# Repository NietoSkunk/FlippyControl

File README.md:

# FlippyControl

Arduino / ESP32 Shield for controlling the [Luminator MAX3000](https://github.com/NietoSkunk/FlippyDriver) Flip Dot driver.

In addition to connecting the appropriate pins of the microcontroller to the data harness, it also includes pads to connect two Wii Extension Controllers (including Classic Controller, Pro Controller, etc), a USB-C 5V power input, and selectable Vcc outputs.

## Cloning repository (with Submodules)

```bash
$ git clone --recurse-submodules git@github.com:NietoSkunk/FlippyControl.git
```

## Production notes

* Only one MCU should be connected at a time.

## Data Harness

| Pin | # | # | Pin |
| --- | - | - | --- |
| VCC | 1 | 2 | GND |
| MOSI | 3 | 4 | PULSE_ENABLE |
| LATCH | 5 | 6 | COL_PULSE_N |
| CLK | 7 | 8 | ROW_PULSE_N |
| RESET | 9 | 10 | LED PWM |
| 5V Return | 11 | 12 | GND |

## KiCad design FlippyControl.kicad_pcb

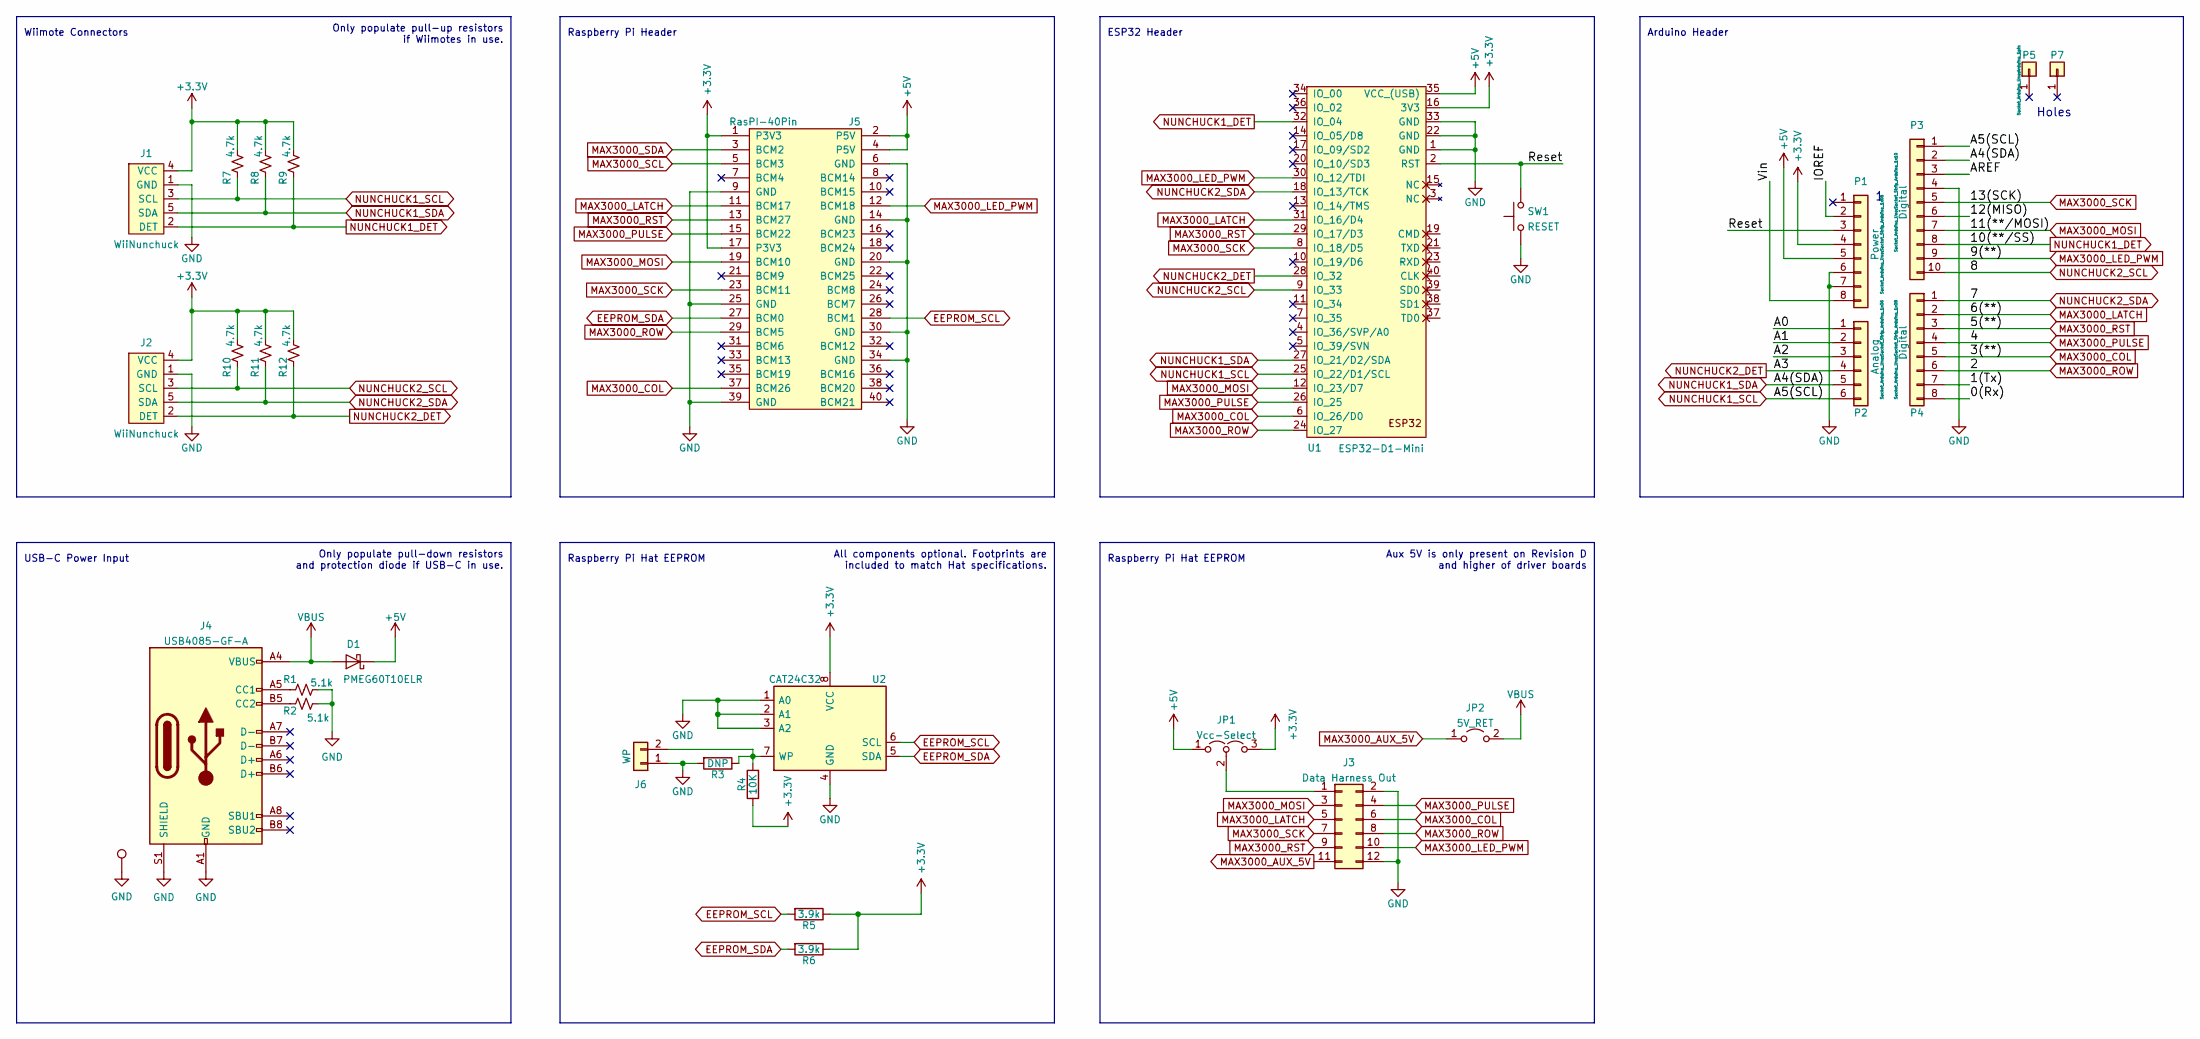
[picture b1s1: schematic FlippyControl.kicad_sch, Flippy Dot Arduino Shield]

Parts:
D1: PMEG60T10ELR; D_SOD-123
J1, J2: WiiNunchuck
J3: Data Harness Out; IDC-Header_2x06_P2.54mm_Vertical
J4: USB4085-GF-A; USB_C_Receptacle_GCT_USB4085
J5: RasPI-40Pin; IDC-Header_2x20_P2.54mm_Vertical
J6: WP; PinHeader_1x02_P2.54mm_Vertical
JP1: Vcc-Select; PinHeader_1x03_P2.54mm_Vertical
JP2: 5V_RET; PinHeader_1x02_P2.54mm_Vertical
P1: Power; Socket_Strip_Arduino_1x08
P2: Analog; Socket_Strip_Arduino_1x06
P3: Digital; Socket_Strip_Arduino_1x10
P4: Digital; Socket_Strip_Arduino_1x08
P5, P7: CONN_01X01; Arduino_1pin
R1, R2: 5.1k; R_0603_1608Metric
R3: DNP; R_0603_1608Metric
R4: 10K; R_0603_1608Metric
R5, R6: 3.9k; R_0603_1608Metric
R7, R8, R9, R10, R11, R12: 4.7k; R_0603_1608Metric
SW1: RESET; SW_SPST_PTS645
TP7: GND; TestPoint_Keystone_5005-5009_Compact
U1: ESP32-D1-Mini; ESP32_mini
U2: CAT24C32; SOIC-8_3.9x4.9mm_P1.27mm

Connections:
+3V3: J1.4 (VCC), J2.4 (VCC), J5.1 (P3V3), J5.17 (P3V3), JP1.3 (B), P1.4, R4.1, R5.1, R6.1, R7.2, R8.2, R9.2, R10.2, R11.2, R12.2, U1.16 (3V3), U2.8 (VCC)
+5V: D1.1 (K), J5.2 (P5V), J5.4 (P5V), JP1.1 (A), P1.5, U1.35 (VCC_(USB))
/0(Rx): P4.8
/1(Tx): P4.7
/12(MISO): P3.6
/A0: P2.1
/A1: P2.2
/A2: P2.3
/AREF: P3.3
/IOREF: P1.2
/Reset: P1.3, SW1.2, U1.2 (RST)
/Vin: P1.8
EEPROM_SCL: J5.28 (BCM1), R5.2, U2.6 (SCL)
EEPROM_SDA: J5.27 (BCM0), R6.2, U2.5 (SDA)
GND: J1.1 (GND), J2.1 (GND), J3.2, J3.12, J4.A1 (GND), J4.A12 (GND), J4.B1 (GND), J4.B12 (GND), J4.S1 (SHIELD), J5.6 (GND), J5.9 (GND), J5.14 (GND), J5.20 (GND), J5.25 (GND), J5.30 (GND), J5.34 (GND), J5.39 (GND), J6.1, P1.6, P1.7, P3.4, R1.2, R2.2, R3.2, SW1.1, TP7.1, U1.1 (GND), U1.22 (GND), U1.33 (GND), U2.1 (A0), U2.2 (A1), U2.3 (A2), U2.4 (GND)
MAX3000_AUX_5V: J3.11, JP2.1 (A)
MAX3000_COL: J3.6, J5.37 (BCM26), P4.5, U1.6 (IO_26/D0)
MAX3000_LATCH: J3.5, J5.11 (BCM17), P4.2, U1.31 (IO_16/D4)
MAX3000_LED_PWM: J3.10, J5.12 (BCM18), P3.9, U1.30 (IO_12/TDI)
MAX3000_MOSI: J3.3, J5.19 (BCM10), P3.7, U1.12 (IO_23/D7)
MAX3000_PULSE: J3.4, J5.15 (BCM22), P4.4, U1.26 (IO_25)
MAX3000_ROW: J3.8, J5.29 (BCM5), P4.6, U1.24 (IO_27)
MAX3000_RST: J3.9, J5.13 (BCM27), P4.3, U1.29 (IO_17/D3)
MAX3000_SCK: J3.7, J5.23 (BCM11), P3.5, U1.8 (IO_18/D5)
MAX3000_SCL: J5.5 (BCM3)
MAX3000_SDA: J5.3 (BCM2)
NUNCHUCK1_DET: J1.2 (DET), P3.8, R9.1, U1.32 (IO_04)
NUNCHUCK1_SCL: J1.3 (SCL), P2.6, P3.1, R7.1, U1.25 (IO_22/D1/SCL)
NUNCHUCK1_SDA: J1.5 (SDA), P2.5, P3.2, R8.1, U1.27 (IO_21/D2/SDA)
NUNCHUCK2_DET: J2.2 (DET), P2.4, R12.1, U1.28 (IO_32)
NUNCHUCK2_SCL: J2.3 (SCL), P3.10, R10.1, U1.9 (IO_33)
NUNCHUCK2_SDA: J2.5 (SDA), P4.1, R11.1, U1.18 (IO_13/TCK)
unnamed: J3.1, JP1.2 (C)
unnamed: J4.A5 (CC1), R1.1
unnamed: J4.B5 (CC2), R2.1
unnamed: J6.2, R3.1, R4.2, U2.7 (WP)
VBUS: D1.2 (A), J4.A4 (VBUS), J4.A9 (VBUS), J4.B4 (VBUS), J4.B9 (VBUS), JP2.2 (B)

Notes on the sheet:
All components optional. Footprints are included to match Hat specifications.
Aux 5V is only present on Revision D and higher of driver boards
Only populate pull-up resistors if Wiimotes in use.
Raspberry Pi Hat EEPROM
ESP32 Header
Raspberry Pi Header
Holes
Wiimote Connectors
Only populate pull-down resistors and protection diode if USB-C in use.
USB-C Power Input
Arduino Header

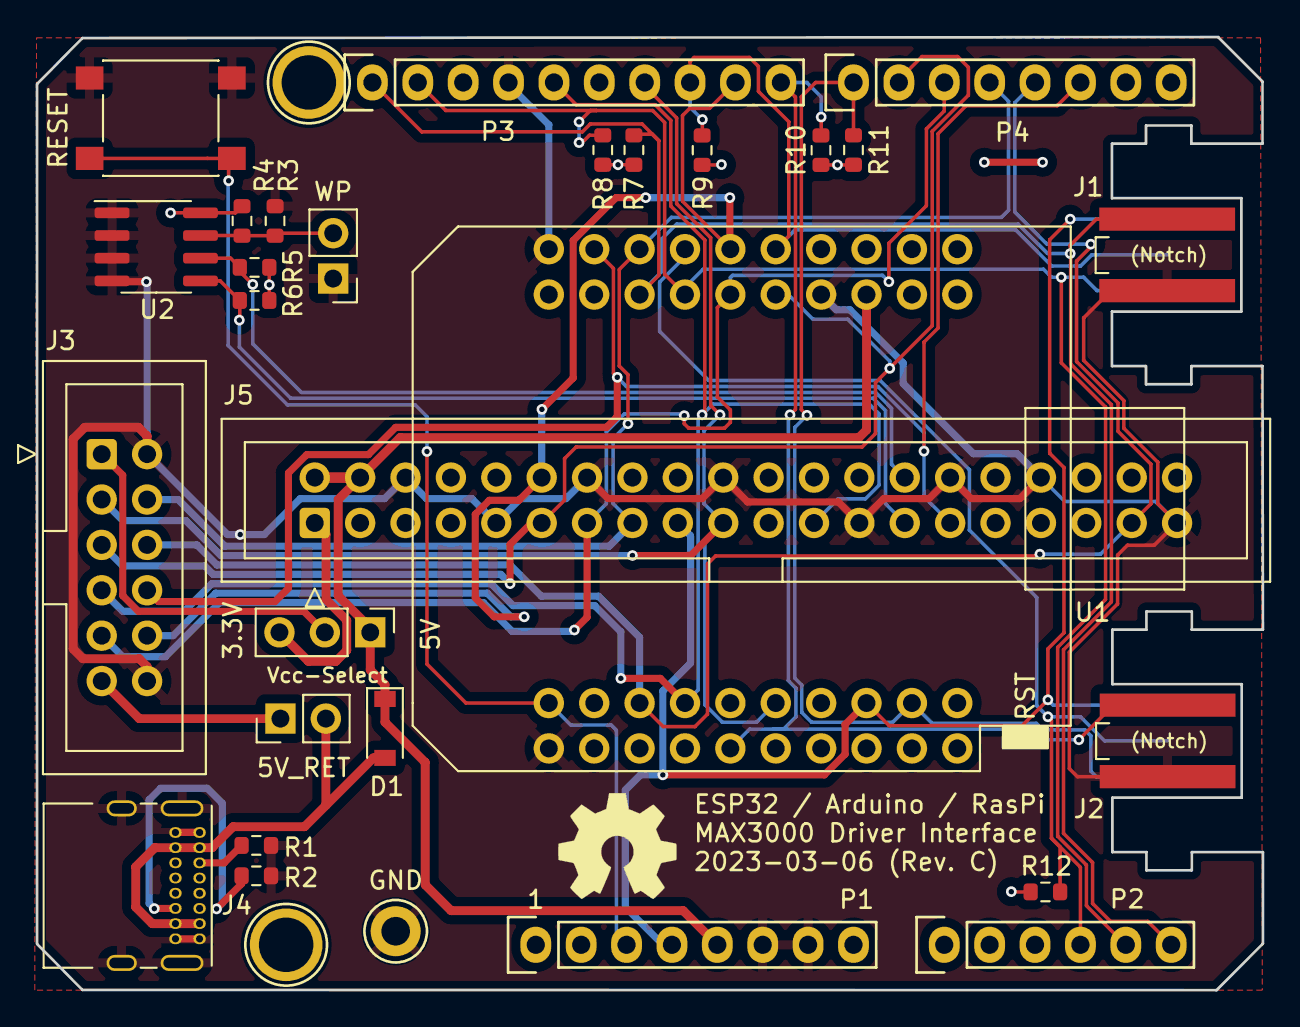
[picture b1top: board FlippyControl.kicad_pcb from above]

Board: 2 copper layers, 68.6 x 53.3 mm, 31 parts (0 on the bottom side), 26 nets.

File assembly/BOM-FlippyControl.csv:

Comment,Designator,Footprint,LCSC
GND,TP7,TestPoint_Keystone_5005-5009_Compact,
ESP32-D1-Mini,U1,ESP32_mini,
Power,P1,Socket_Strip_Arduino_1x08,
Analog,P2,Socket_Strip_Arduino_1x06,
Digital,P3,Socket_Strip_Arduino_1x10,
Digital,P4,Socket_Strip_Arduino_1x08,
CONN_01X01,P5,Arduino_1pin,
CONN_01X01,P7,Arduino_1pin,
PMEG60T10ELR,D1,D_SOD-123,
USB4085-GF-A,J4,USB_C_Receptacle_GCT_USB4085,
Data Harness Out,J3,IDC-Header_2x06_P2.54mm_Vertical,
Vcc-Select,JP1,PinHeader_1x03_P2.54mm_Vertical,
5.1k,R2,R_0603_1608Metric,
5.1k,R1,R_0603_1608Metric,
DNP,R3,R_0603_1608Metric,
10K,R4,R_0603_1608Metric,
RESET,SW1,SW_SPST_PTS645,
5V_RET,JP2,PinHeader_1x02_P2.54mm_Vertical,
WP,J6,PinHeader_1x02_P2.54mm_Vertical,
3.9k,R5,R_0603_1608Metric,
RasPI-40Pin,J5,IDC-Header_2x20_P2.54mm_Vertical,
3.9k,R6,R_0603_1608Metric,
CAT24C32,U2,SOIC-8_3.9x4.9mm_P1.27mm,
4.7k,R12,R_0603_1608Metric,
4.7k,R11,R_0603_1608Metric,
4.7k,R10,R_0603_1608Metric,
4.7k,R9,R_0603_1608Metric,
4.7k,R8,R_0603_1608Metric,
4.7k,R7,R_0603_1608Metric,

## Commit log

2022-08-17 Initial revision of FlippyControl
2022-08-17 Add missing Schematic PDF
2022-08-25 Add submodule and migrate project
2022-08-31 Final Rev.B, adding RasPi connector and PWM output
2022-08-31 Update images for Rev B
2023-03-07 Add pullups, fix miswired pads
